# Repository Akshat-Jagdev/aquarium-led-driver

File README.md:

# Aquarium LED Driver Panel (V0)

Open-source hardware project: a scientifically engineered aquarium LED light for fish-colour enhancement, designed for low-cost manufacture in India.

**What this repo contains — the complete engineering package:**
- **Hardware**: KiCad 8 sources for a 4-board panel (2 MCPCB LED-board designs × 2 + driver board), dual-rail +24 V/+12 V, DRC-clean layouts with scripted netlist verification
- **Firmware**: ESP32-C3 Arduino sketches — 4 light profiles, 2 kHz / 12-bit PWM, per-channel dimming
- **Engineering tools** (Python): power/thermal calculator, PWM frequency analyser, LED lifetime estimator, BOM cost calculator
- **Test procedures**: TP-01 → TP-07 (bench bring-up, optical comparison, 2-hr thermal soak, spectrum, 100-hr reliability)
- **Documentation**: design-decision rationale, driver-architecture audit (AL8860 buck topology), risk register, schematic
- **Business analysis**: unit economics, volume cost projections, competitive landscape, go-to-market

> **Stage**: V0 prototype — all 4 PCBs routed and verified, panel fabricated and received (Oct 2026); bench bring-up in progress.
> **Target retail**: ₹3,000–4,000 · **Production BOM (incl. LEDs)**: ~₹2,542 @ qty 500, ~₹2,340 @ qty 1000 · **Target**: ≤₹2,000 @ qty 5000+

---

## 1. Project Structure

```
aquarium_v0/
├── README.md                      ← this file (master index)
│
├── docs/
│   ├── 00_project_brief.md        ← full business + product specification
│   ├── 01_design_decisions.md     ← all design choices and their rationale
│   ├── 02_audit_report.md         ← full audit of original AL8860 architecture
│   ├── 03_schematic_text.md       ← text-form schematic of V0
│   └── 04_risk_register.md        ← known risks and how to mitigate them
│
├── hardware/
│   ├── kicad_project/             ← KiCad 8 sources (schematic + 4-board PCB layout)
│   ├── mechanical/
│   │   ├── extrusion_dims.md      ← aluminium extrusion specifications
│   │   ├── pcb_layout_notes.md    ← critical PCB layout rules
│   │   └── assembly_drawing.md    ← mechanical assembly
│
├── firmware/
│   ├── pwm_test_sketch.ino        ← ESP32-C3 PWM control (4 profiles, 2 kHz)
│   ├── esp32_pin_map.md           ← ESP32-C3 pin assignment
│   └── build_instructions.md      ← how to compile and upload
│
├── bom/
│   ├── BOM_v0_prototype.csv       ← bill of materials, 1-unit pricing
│   ├── BOM_v0_production_500.csv  ← bill of materials, 500-unit pricing
│   ├── PARTS_LIST.md              ← complete parts list with verified links (all sources)
│   ├── india_suppliers.md         ← contact list for Indian distributors
│   ├── lcsc_links.md              ← direct LCSC links for every part
│   └── digikey_mouser_links.md    ← backup sourcing for parts not on LCSC
│
├── datasheets/
│   ├── AL8860_diodes.pdf          ← driver IC
│   ├── LUXEON_5050_HE_Plus.pdf    ← white LED
│   ├── LUXEON_2835_Red.pdf        ← 625 nm LED
│   ├── LUXEON_Rubix_448.pdf       ← blue LED
│   ├── LUXEON_SunPlus_660.pdf     ← deep-red LED
│   ├── LRS-35-24_meanwell.pdf     ← PSU
│   ├── WSL2512_vishay.pdf         ← current-sense resistors
│   ├── 7447783680_wurth.pdf       ← inductor
│   └── SS3100_diodes.pdf          ← schottky diode
│
├── test_procedures/
│   ├── TP-01_one_channel_bench.md ← validate ONE AL8860 on perfboard
│   ├── TP-02_full_pcb_bench.md    ← validate full V0 PCB
│   ├── TP-03_optical_compare.md   ← compare profiles A/B/C/D visually
│   ├── TP-04_thermal_2hr.md       ← 2-hour thermal soak test
│   ├── TP-05_spectrum_test.md     ← spectrometer measurement (when you have one)
│   ├── TP-06_fish_appearance.md   ← qualitative test with ornamental fish
│   └── TP-07_reliability_soak.md  ← extended run (target 100 hr)
│
├── business/
│   ├── competitive_landscape.md   ← TICA vs Chihiros vs others
│   ├── unit_economics.md          ← per-unit cost and margin model
│   ├── volume_projection.md       ← 1 / 100 / 500 / 1000 unit cost
│   └── go_to_market.md            ← retail / e-commerce / aquarium shops
│
└── tools/
    ├── power_thermal_calculator.py
    ├── bom_cost_calculator.py
    ├── pwm_freq_analyzer.py
    └── led_lifetime_estimator.py
```

---

## 2. Quick Start (Layman)

If you are new to this project and want to start building today:

1. **Read** `docs/00_project_brief.md` (15 min) — full picture
2. **Read** `docs/02_audit_report.md` (20 min) — what to build and WHY
3. **Read** `docs/03_schematic_text.md` (15 min) — exact wiring
4. **Open** `bom/BOM_v0_prototype.csv` (5 min) — list of parts to order
5. **Order parts** from `bom/PARTS_LIST.md` (complete parts list with verified links for every component, including LEDs) and `bom/lcsc_links.md` and `bom/india_suppliers.md`
6. **Follow** `test_procedures/TP-01_one_channel_bench.md` — build ONE channel first
7. **Run** `tools/power_thermal_calculator.py` — verify numbers any time
8. **When ONE channel works** → move to full KiCad PCB design

---

## 3. Critical Numbers (cheat sheet)

| Item | Value |
|------|-------|
| Input voltage | 24 V DC |
| Total power (all channels max) | ~22 W |
| PSU current (full load) | ~0.92 A |
| White current per string | 250 mA |
| Red current | 120 mA |
| Blue current | 303 mA (start conservative) |
| Deep red current | 120 mA |
| PWM frequency | 2 kHz (NOT 400 Hz) |
| PWM resolution | 12-bit |
| AL8860 count | 7 (4 white, 1 red, 1 blue, 1 deep red) |
| RSET (white / red / blue / DR) | 0.40 / 0.82 / 0.33 / 0.82 Ω |
| Inductor | 68 µH shielded, ≥0.95 A Isat |
| Schottky | 100 V / 3 A (SS3100) — NOT SS24 |
| Input cap | 22 µF / 50 V X7R 1210 (NOT 10 µF 0805) |
| LED TC limit | 85 °C |
| Fuse | 2 A slow-blow |
| Controller | ESP32-C3 SuperMini, direct GPIO → 1 kΩ → CTRL |
| (NO 2N7002) | — |

---

## 4. What you already own (or have ordered)

- 12× White LED: Luminus MP5050-240P (5700K)
- 4× Red LED: LUXEON 2835 Red 625 nm
- 2× Royal Blue LED: Cree XPGDRY-LS-0000-00501
- 2× Deep Red LED: LUXEON SunPlus 660 nm
- 1× Mean Well LRS-35-24
- 1× ESP32-C3 SuperMini

---

## 5. What you still need to order

See `bom/BOM_v0_prototype.csv` and `bom/lcsc_links.md`. Total estimate: **₹3,500–4,000** for the prototype (1 unit) including passive components, PCB, and mechanical parts.

---

## 6. Current status

- [x] Architecture defined
- [x] LEDs selected and ordered
- [x] PSU selected and ordered
- [x] Controller selected and ordered
- [x] Driver IC selected
- [x] Audit of driver architecture complete
- [x] Schematic text written
- [x] BOM with India sourcing prepared
- [x] BOM production-500 ready
- [x] PWM firmware written
- [x] Python calculators written (all 4 tools verified to run)
- [x] Test procedures drafted (TP-01 → TP-07)
- [x] Hardware mechanical documentation drafted (extrusion, PCB layout, assembly)
- [x] ESP32 pin map + build instructions
- [x] KiCad project scaffold documented
- [x] Business documents drafted (competitive landscape, unit economics, volume projection, go-to-market)
- [x] Risk register drafted
- [x] Design-decision rationale written
- [x] KiCad schematic capture (aquarium_v0.kicad_sch, Sep 14 netlist is truth)
- [x] 4-board PCB layout routed (gen_pcb.py + ROUTES_EXTRA.json; DRC clean on all boards, verify_netlist.py passes)
- [x] MCPCB + driver PCB Gerbers — panel fabricated and received (Oct 2026); see `hardware/assembly/`
- [ ] One-channel bench prototype (Phase B)
- [ ] Full PCB prototype (Phase C)
- [ ] Optical test against TICA (TP-03)
- [ ] Thermal verification (TP-04)
- [ ] Spectrum measurement (TP-05)
- [ ] Reliability soak (TP-07)
- [ ] Production design (V1)

---

## 7. Design decisions (resolved)

Before PCB layout, decide:
- Length: 60 cm or 90 cm? (DECIDED: 60 cm)
- Diffuser: clear, opal, or both? (DECIDED: opal)
- MCPCB: **DECIDED** — 4 small boards, 2 designs × 2 (5-LED, 140 × 20 mm; see `extrusion_dims.md` §3)
- Mounting: hanging kit, rim-mount bracket, or both? (DECIDED: rim-mount bracket)

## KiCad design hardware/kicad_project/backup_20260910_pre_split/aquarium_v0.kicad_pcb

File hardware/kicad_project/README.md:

# KiCad Project — V0 Aquarium Light

> Scaffold for the V0 schematic capture and PCB layout.
> Create the `.kicad_pro` and `.kicad_sch` in KiCad 8 and save them here.

## 1. How to create the project

1. Open **KiCad 8** (project editor).
2. **File → New Project** → name it `aquarium_v0` → save into this folder.
3. KiCad creates:
   - `aquarium_v0.kicad_pro` — project settings
   - `aquarium_v0.kicad_sch` — top-level schematic (initially empty)
4. Use **Schematic Editor → File → Add Sheet** to break the schematic into
   sections (recommended for readability):
   - `01_power.kicad_sch` — input, fuse, switch, 24 V bus, ESP32 power tree
   - `02_white_drivers.kicad_sch` — 4× AL8860 white channels
   - `03_colour_drivers.kicad_sch` — red + blue + deep-red AL8860 channels
   - `04_esp32_interface.kicad_sch` — ESP32 header + GPIO buffer network

## 2. Library plan

| Part | Source |
|------|--------|
| AL8860W6-7 (SOT23-6) | Diodes Inc KiCad library, or generic SOT-23-6 symbol with custom footprint |
| Würth 7447783680 (WE-PD series) | Würth WE-PD library, or KiCad "Inductor_SMD" + manual WE-PD footprint |
| Vishay WSL2512 | KiCad `Resistor_SMD:R_2512_6332Metric` |
| SS3100 (SMA) | KiCad `Diode_SMD:D_SMA` |
| ESP32-C3 SuperMini | Custom symbol + custom footprint (no KiCad library entry) |
| LUXEON 5050, 2835, Rubix | Custom symbols + footprints (see below) |
| 220 µF Nichicon UPW radial | KiCap `CP_Radial_D10.0mm_P5.00mm` or similar |
| Mean Well LRS-35-24 | Mechanical only — represented as off-board connector |
| IRM-02-5 | Off-board DIP module — represented as 4-pin connector |

## 3. Custom symbol / footprint list

You'll need to draw these by hand using KiCad's Symbol Editor and
Footprint Editor:

1. **ESP32-C3 SuperMini module**
   - Symbol: 1×6 header with `5V, GPIO0, GPIO1, GND, 3V3, ...` pins
   - Footprint: 2× 1×12 pin header strip, 2.54 mm pitch, board-edge
     mounting
2. **LUXEON 5050 HE Plus**
   - Symbol: LED with anode / cathode / thermal pad
   - Footprint: 5050 SMD with thermal pad
3. **LUXEON 2835 (Red and SunPlus)**
   - Symbol: LED with anode / cathode / thermal pad
   - Footprint: 2835 SMD
4. **LUXEON Rubix (L1RX-RYL1000000000)**
   - Symbol: LED with 2 anode + 2 cathode + thermal pad
   - Footprint: Rubix-style SMD with thermal pad

## 4. Net classes

Define these in **Project → Design Rules → Net Classes**:

| Net class | Clearance | Track width | Via drill | Use |
|-----------|-----------|-------------|-----------|-----|
| Default | 0.15 mm | 0.20 mm | 0.3 mm | Signals, CTRL, 3V3 |
| Power_24V | 0.30 mm | 0.50 mm | 0.5 mm | 24 V bus |
| LED_Anode | 0.30 mm | 1.00 mm | 0.5 mm | LED anode traces (250 mA) |
| LED_Cathode | 0.30 mm | 0.80 mm | 0.5 mm | LED cathode / RSET |

## 5. Layout checklist (before generating Gerbers)

- [ ] Board outline: ~580 × ≤14 mm slender strip (extrusion cavity) — see
      `../mechanical/pcb_layout_notes.md` §1
- [ ] MCPCB headers J2–J5: 6-pin each, pinout per `pcb_layout_notes.md` §3.2
      (colour series chains completed with PCB traces between headers)
- [ ] All decoupling caps within 2 mm of their IC pin (AL8860 × 7)
- [ ] Switching loop (LX, L, D1) area < 50 mm² per channel
- [ ] 100 mm² thermal copper under each AL8860, stitched with vias
- [ ] ESP32 section separated from 24 V section by ≥ 10 mm
- [ ] All MCPCB connectors labelled + and −
- [ ] Fuse clearly marked F1 with value
- [ ] Mounting holes dimensioned and clear of copper
- [ ] DRC clean, no warnings

## 6. Fabrication output

Export Gerbers + drill files into `hardware/kicad_project/gerbers/` and
zip them before uploading to JLCPCB / PCBWay. Use these settings:

- Layers: top, bottom, silkscreen top, soldermask top + bottom
- 1.6 mm board thickness
- 1 oz copper
- HASL-lead-free finish (cheapest) or ENIG (better for hand soldering)
- 4× M3 mounting holes plated (or non-plated — cheaper, fine for our use)

## 7. Open items

- Final ESP32-C3 SuperMini symbol/footprint geometry — measure from the
  physical board before drawing
- Confirm Mean Well IRM-02-5 pinout from datasheet before symbolising
- Decide whether to use 2 oz copper for the LED anode traces (cleaner
  at high current, +₹30 per board)

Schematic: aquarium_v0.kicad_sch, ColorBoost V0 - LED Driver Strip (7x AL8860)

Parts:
C1, C20, C21, C22, C23, C24, C25, C26: 100nF; C_0603_1608Metric
C2: 220uF/50V; CP_Radial_D10.0mm_P5.00mm
C3, C4: 1uF; C_0805_2012Metric
C10, C11, C12, C13, C14, C15, C16: 22uF; C_1210_3225Metric
D1, D2, D3, D4, D5, D6, D7: SS3100; D_SMA
F1: 2A slow-blow; Fuseholder_Clip-5x20mm_Littelfuse_520_Inline_P20.50x5.80mm_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
J1: DC 24V IN; TerminalBlock_MaiXu_MX126-5.0-02P_1x02_P5.00mm
J2: MCPCB1 (L1, blue); PinHeader_1x06_P2.54mm_Vertical
J3: MCPCB2 (L2, blue); PinHeader_1x06_P2.54mm_Vertical
J4: MCPCB3 (R1, deep-red); PinHeader_1x06_P2.54mm_Vertical
J5: MCPCB4 (R2, deep-red); PinHeader_1x06_P2.54mm_Vertical
J6: ESP32-C3; PinHeader_1x06_P2.54mm_Vertical
J7: SW LOOP; TerminalBlock_MaiXu_MX126-5.0-02P_1x02_P5.00mm
L1, L2, L3, L4, L5, L6, L7: 68uH; L_7.3x7.3_H3.5
MH1, MH2, MH3, MH4: M3; MountingHole_3.2mm_M3
R1, R2, R3, R4: 1k; R_0603_1608Metric
R5, R6, R7, R8: 100k; R_0603_1608Metric
R10, R11, R12, R13: 0.40R; R_2512_6332Metric
R14, R16: 0.82R; R_2512_6332Metric
R15: 0.33R; R_2512_6332Metric
U1, U2, U3, U4, U5, U6, U7: AL8860WT-7; TSOT-23-5
U8: IRM-02-5; PinHeader_1x04_P2.54mm_Vertical
U9: AMS1117-3.3; SOT-223

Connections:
+3V3: C4.2, J6.6, U9.2 (VO)
+5V: C3.2, U8.3 (+VOUT), U9.3 (VI)
/B_A: J2.5, R15.1, U6.4 (SET)
/B_J23: J2.6, J3.5
/B_K: J3.6, L6.2
/CTRL_B: R3.1, R7.2, U6.3 (CTRL)
/CTRL_DR: R4.1, R8.2, U7.3 (CTRL)
/CTRL_R: R2.1, R6.2, U5.3 (CTRL)
/CTRL_W: R1.1, R5.2, U1.3 (CTRL), U2.3 (CTRL), U3.3 (CTRL), U4.3 (CTRL)
/DR_A: J4.5, R16.1, U7.4 (SET)
/DR_J45: J4.6, J5.5
/DR_K: J5.6, L7.2
/PWM_B: J6.3, R3.2
/PWM_DR: J6.4, R4.2
/PWM_R: J6.2, R2.2
/PWM_W: J6.1, R1.2
/R_A: J2.3, R14.1, U5.4 (SET)
/R_J23: J2.4, J3.3
/R_J34: J3.4, J4.3
/R_J45: J4.4, J5.3
/R_K: J5.4, L5.2
/SW_A: F1.2, J7.1
/VIN_RAW: F1.1, J1.1
/W1_A: J2.1, R10.1, U1.4 (SET)
/W1_K: J2.2, L1.2
/W2_A: J3.1, R11.1, U2.4 (SET)
/W2_K: J3.2, L2.2
/W3_A: J4.1, R12.1, U3.4 (SET)
/W3_K: J4.2, L3.2
/W4_A: J5.1, R13.1, U4.4 (SET)
/W4_K: J5.2, L4.2
unnamed: D1.2, L1.1, U1.1 (SW)
unnamed: D2.2, L2.1, U2.1 (SW)
unnamed: D3.2, L3.1, U3.1 (SW)
unnamed: D4.2, L4.1, U4.1 (SW)
unnamed: D5.2, L5.1, U5.1 (SW)
unnamed: D6.2, L6.1, U6.1 (SW)
unnamed: D7.2, L7.1, U7.1 (SW)

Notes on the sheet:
POWER INPUT: J1 (panel jack leads) -> F1 2A slow-blow -> J7 (panel switch loop) -> +24V bus
LOGIC POWER: IRM-02-5 24V->5V, AMS1117 5V->3V3. VERIFY IRM-02-5 PINOUT VS DATASHEET.
ESP32-C3 SuperMini plugs onto J6. GPIO0-3 -> 1k -> CTRL_x; 100k pull-downs keep LEDs off during boot.
LED DRIVER CHANNELS (7x AL8860WT-7, TSOT-25). High-side sense: +24V -> RSET -> SET pin = LED string anode; string cathode -> L -> SW; D freewheels SW -> +24V. I_LED = 0.1V / RSET.
MCPCB HEADERS: J2-J5 -> LED boards. Red chain J2>J3>J4>J5, blue J2>J3, deep-red J4>J5 (series joins on this PCB).
AL8860 RESOLVED 2026-09-08: 'AL8860W6-7 SOT-23-6' DOES NOT EXIST (LCSC C460356 = AP3012 boost, wrong part). Use AL8860WT-7 TSOT-25, LCSC C125330. Pinout per DS39014: 1=SW 2=GND 3=CTRL 4=SET 5=VIN.

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
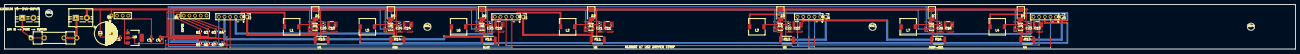
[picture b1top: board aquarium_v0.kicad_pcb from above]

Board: 2 copper layers, 580.0 x 20.0 mm, 68 parts (0 on the bottom side), 40 nets.

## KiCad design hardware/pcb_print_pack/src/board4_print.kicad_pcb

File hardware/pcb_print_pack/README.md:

# DIY PCB Print Pack — aquarium_v0 driver boards (4 boards)

Everything you need to make the 4 driver boards **at home** (toner
transfer or UV photoresist), generated 2026-09-12 from the verified,
DRC-clean split boards. The artwork is byte-equivalent to the fab
boards, only translated so each board sits at an 8 mm margin on an
A4 page (the fab files plot at the original 580 mm-frame coordinates
and run off the page).

```
pcb_print_pack/
├── board1/ … board4/          one folder per board
│   ├── print/                 6 printable PDFs (A4 landscape, 1:1)
│   ├── drill/                 Excellon .drl + hole-map PDF + report
│   └── gerber/                full 7-layer fab set (if you give up
│                              and send them to JLCPCB after all 😉)
└── src/                       the translated KiCad files used to plot
                               everything (open in KiCad to re-plot)
```

| Board | Size (mm) | Vias | Plated holes | Unplated (M3) |
|-------|-----------|------|--------------|----------------|
| 1 | 150.5 × 20 | 31 | 69 | 2 |
| 2 | 149.0 × 20 | 44 | 72 | 2 |
| 3 | 97.9 × 20 | 26 | 52 | 2 |
| 4 | 175.1 × 20 | 34 | 50 | 2 |

## 1. Printing — the one rule that matters

**Print at 100% / "Actual size". Never "fit to page" or "shrink
oversized pages".** Laser printer, highest resolution/darkest setting.

**Scale check (mandatory, every print):** print `boardN_Edge_Cuts.pdf`
and measure the board outline width with a steel ruler:
B1 **150.5 mm**, B2 **149.0 mm**, B3 **97.9 mm**, B4 **175.1 mm**
(±0.2 mm). If it doesn't match, your printer is scaling — fix that
before wasting copper.

## 2. Which PDF for which method

Two copper artwork files per side — the right one depends on how you
apply it:

| Method | Top copper (F.Cu) | Bottom copper (B.Cu) |
|--------|-------------------|----------------------|
| **Toner transfer** (paper laid face-down on the copper) | `boardN_F_Cu_MIRRORED.pdf` | `boardN_B_Cu_BOTTOM-SIDE.pdf` |
| **UV photoresist** (transparency laid on top of the copper) | `boardN_F_Cu_TOP-SIDE.pdf` | `boardN_B_Cu_MIRRORED.pdf` |

For photoresist, print on transparency with the **ink side facing the
board** (flip the film over after printing) so the ink touches the
resist — sharpness.

Other files:
- `boardN_F_Silkscreen.pdf` — component-placement reference. Your home
  board will have no real silkscreen: print this and keep it next to
  you while stuffing. It also shows the board title and pin-1 markers.
- `boardN_Edge_Cuts.pdf` — board outline, also your scale check.
- Ground pours are part of the copper artwork — don't "simplify" them
  away; they carry the GND net.

## 3. Drilling

Hole sizes (from `drill/drill_report.txt` / the map PDF
`boardN_print-drl_map.pdf`):

| Size | Use | Boards | Home-shop advice |
|------|-----|--------|------------------|
| 0.3 mm | signal vias | all | **See §4 — do NOT hand-drill 0.3 mm.** |
| 1.0 mm | header/component pins (J1–J13) | all | 1.0 mm carbide bit |
| 1.3 mm | fuse clips (F1) | 1 only | 1.3 mm bit |
| 3.2 mm | M3 mounting holes (NPTH) | all | 3.2 mm; use as top/bottom **alignment pins** |

Drill AFTER etching, BEFORE solder mask/assembly. Use the drill-map
PDF as your hole template; a small drill press beats a hand drill —
the board is only 20 mm wide, so mark hole centers with a center punch
first.

## 4. The vias — read this before etching

The 0.3 mm via drill is at the limit of home tooling, and a via pad is
only 0.8 mm across — **oversizing the hole to 0.6–0.8 mm eats the
whole annular ring**. The reliable home method is **through-wire vias**:

1. Drill the vias at 0.6–0.8 mm (don't try 0.3 mm).
2. Thread each via with a strand of tinned copper wire (unwrap a
   strand from stranded wire, or use resistor-lead clippings).
3. Solder BOTH sides, then snip flush.

31/44/26/34 vias on boards 1–4 — an evening of threading. There is no
via on this board you can skip: the CTRL ladder and colour chains
change layers through them.

## 5. Two-layer alignment

- Etch the top side first, then flip the SAME copper-clad board for
  the bottom.
- Use the two 3.2 mm M3 holes as registration: after etching top,
  push two 3.2 mm pins (or drill bits) through and align the bottom
  artwork/film to them before exposure/transfer.
- Boards are 20 mm wide and all vias are through-wired, so a small
  top/bottom offset (<0.3 mm) is tolerable — but check before etching,
  not after.

## 6. Honest warnings

- **Min track 0.25 mm / min clearance 0.25 mm** (signal netclass).
  Toner transfer can do this, but you need a clean, hot transfer —
  laser printer + glossy paper (or the blue PnP sheets), no inkjet.
  If 0.25 mm traces lift, stop and troubleshoot the transfer; don't
  accept broken signal traces. Power tracks are 0.5–1.0 mm — easy.
- **No solder mask**: the 2 kHz buck converters will survive hand
  soldering without mask, but avoid solder bridges on the 0603
  passives; flux generously and inspect under magnification.
- **The LED MCPCBs cannot be made at home** (aluminum core) — order
  those from a fab as before (see `bom/PARTS_LIST.md` §10.2).
- **U8, U9, C3, C4 on board 1 stay unpopulated** (V0 decision,
  ESP32 USB-powered) — etch them anyway, just don't stuff them.
- The joints between boards need J8–J13 pin headers + 3 jumper
  harnesses (see `hardware/mechanical/pcb_layout_notes.md` §3.4) —
  a home-made board is fine for this; the headers are ordinary 2.54 mm
  breakaway strip.
- If a board gets ruined, the `gerber/` folder per board is a complete
  fab set — you can always send just that board to JLCPCB.

## 7. Verification you can do at home

1. Multimeter continuity: +24V pad to each RSET pin-2, GND ring
   continuity across the pour, no +24V-to-GND shorts before the
   drivers are stuffed.
2. Eyeball every trace against `boardN_F_Silkscreen.pdf` /
   the drill map under a loupe.
3. Before full population: install only the power path on board 1
   (F1, C2, J1), apply 24 V, check the fuse and no heat.
4. Then follow TP-02 (full PCB bench test) in the test plan.

## 8. Where this came from

- Source of truth: `hardware/kicad_project/aquarium_v0_board{1..4}.kicad_pcb`
  (DRC 0/0, `verify_pcb.py --board N` ALL PASS ×4, byte-reproducible).
- These print files were generated from translated copies
  (`src/board{N}_print.kicad_pcb`, outline anchored at 8 mm on A4)
  by `hardware/kicad_project/make_print_copies.py`; the translation
  is machine-verified by `check_print_copies.py` — every pad, track,
  via and zone moved by exactly the same offset, DRC re-checked 0/0.
- Regenerate everything: run `make_print_copies.py`, then re-run the
  kicad-cli exports (see the commands in the project checklist).

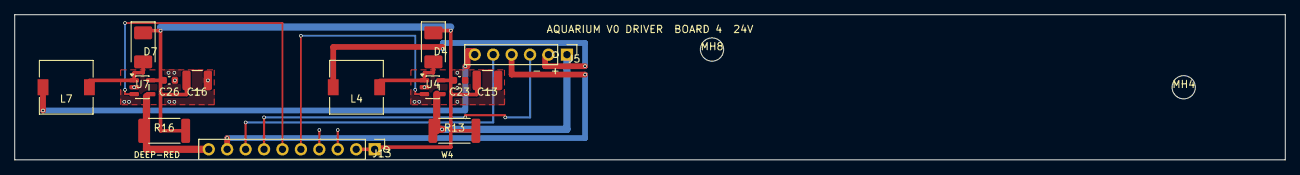
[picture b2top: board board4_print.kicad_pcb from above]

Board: 2 copper layers, 175.1 x 20.0 mm, 16 parts (0 on the bottom side), 13 nets.

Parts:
C13, C16: 22uF; C_1210_3225Metric
C23, C26: 100nF; C_0603_1608Metric
D4, D7: SS3100; D_SMA
J5: MCPCB4 (R2, deep-red); PinHeader_1x06_P2.54mm_Vertical
J13: B4-W -> J12; PinHeader_1x10_P2.54mm_Vertical
L4, L7: 68uH; L_7.3x7.3_H3.5
MH4, MH8: M3; MountingHole_3.2mm_M3
R13: 0.40R; R_2512_6332Metric
R16: 0.82R; R_2512_6332Metric
U4, U7: AL8860WT-7; TSOT-23-5

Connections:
+24V: C13.2, C16.2, C23.2, C26.2, D4.1, D7.1, J13.1, J13.2, R13.2, R16.2, U4.5, U7.5
/CTRL_DR: J13.6, U7.3
/CTRL_W: J13.5, U4.3
/DR_A: J13.10, R16.1, U7.4
/DR_J45: J5.5, J13.8
/DR_K: J5.6, L7.2
/R_J45: J5.3, J13.7
/R_K: J5.4, J13.9
/W4_A: J5.1, R13.1, U4.4
/W4_K: J5.2, L4.2
GND: C13.1, C16.1, C23.1, C26.1, J13.3, J13.4, U4.2, U7.2
unnamed: D4.2, L4.1, U4.1
unnamed: D7.2, L7.1, U7.1

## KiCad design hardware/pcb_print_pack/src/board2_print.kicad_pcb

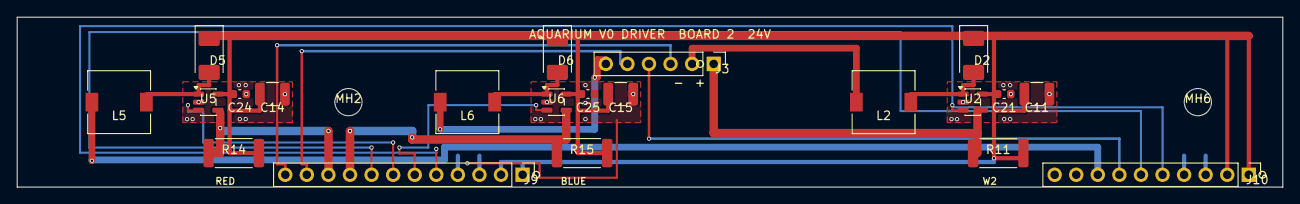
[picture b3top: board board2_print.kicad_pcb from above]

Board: 2 copper layers, 149.0 x 20.0 mm, 23 parts (0 on the bottom side), 18 nets.

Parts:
C11, C14, C15: 22uF; C_1210_3225Metric
C21, C24, C25: 100nF; C_0603_1608Metric
D2, D5, D6: SS3100; D_SMA
J3: MCPCB2 (L2, blue); PinHeader_1x06_P2.54mm_Vertical
J9: B2-W -> J8; PinHeader_1x12_P2.54mm_Vertical
J10: B2-E -> J11; PinHeader_1x10_P2.54mm_Vertical
L2, L5, L6: 68uH; L_7.3x7.3_H3.5
MH2, MH6: M3; MountingHole_3.2mm_M3
R11: 0.40R; R_2512_6332Metric
R14: 0.82R; R_2512_6332Metric
R15: 0.33R; R_2512_6332Metric
U2, U5, U6: AL8860WT-7; TSOT-23-5

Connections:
+24V: C11.2, C14.2, C15.2, C21.2, C24.2, C25.2, D2.1, D5.1, D6.1, J9.1, J9.2, J10.1, J10.2, R11.2, R14.2, R15.2, U2.5, U5.5, U6.5
/B_A: J9.9, R15.1, U6.4
/B_J23: J3.5, J9.11
/B_K: J3.6, L6.2
/CTRL_B: J9.6, U6.3
/CTRL_DR: J9.8, J10.6
/CTRL_R: J9.7, U5.3
/CTRL_W: J9.5, J10.5, U2.3
/R_A: J9.10, R14.1, U5.4
/R_J23: J3.3, J9.12
/R_J34: J3.4, J10.7
/R_K: J10.8, L5.2
/W2_A: J3.1, R11.1, U2.4
/W2_K: J3.2, L2.2
GND: C11.1, C14.1, C15.1, C21.1, C24.1, C25.1, J9.3, J9.4, J10.3, J10.4, U2.2, U5.2, U6.2
unnamed: D2.2, L2.1, U2.1
unnamed: D5.2, L5.1, U5.1
unnamed: D6.2, L6.1, U6.1

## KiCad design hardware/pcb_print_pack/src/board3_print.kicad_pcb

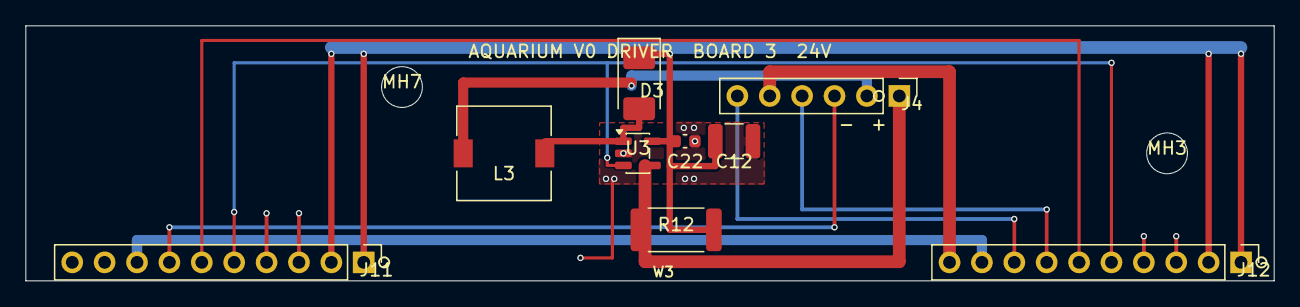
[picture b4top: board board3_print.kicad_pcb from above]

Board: 2 copper layers, 97.9 x 20.0 mm, 11 parts (0 on the bottom side), 12 nets.

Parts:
C12: 22uF; C_1210_3225Metric
C22: 100nF; C_0603_1608Metric
D3: SS3100; D_SMA
J4: MCPCB3 (R1, deep-red); PinHeader_1x06_P2.54mm_Vertical
J11: B3-W -> J10; PinHeader_1x10_P2.54mm_Vertical
J12: B3-E -> J13; PinHeader_1x10_P2.54mm_Vertical
L3: 68uH; L_7.3x7.3_H3.5
MH3, MH7: M3; MountingHole_3.2mm_M3
R12: 0.40R; R_2512_6332Metric
U3: AL8860WT-7; TSOT-23-5

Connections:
+24V: C12.2, C22.2, D3.1, J11.1, J11.2, J12.1, J12.2, R12.2, U3.5
/CTRL_DR: J11.6, J12.6
/CTRL_W: J11.5, J12.5, U3.3
/DR_A: J4.5, J12.10
/DR_J45: J4.6, J12.8
/R_J34: J4.3, J11.7
/R_J45: J4.4, J12.7
/R_K: J11.8, J12.9
/W3_A: J4.1, R12.1, U3.4
/W3_K: J4.2, L3.2
GND: C12.1, C22.1, J11.3, J11.4, J12.3, J12.4, U3.2
unnamed: D3.2, L3.1, U3.1

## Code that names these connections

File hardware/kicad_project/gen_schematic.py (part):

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# J1: DC 24V in (panel jack leads -> screw terminal)
conn("aquarium:Conn_01x02", 1500, 2500, "J1", "DC 24V IN", TB2, 2)
wire(1500, 2500, 1500, 2600)
label("VIN_RAW", 1500, 2600)
pwr("GND", 1500, 2400)
pwr("PWR_FLAG", 1500, 2400)

# F1: fuse (5x20mm clip-in, Keystone 3527-style clips)
comp2("aquarium:Fuse", 2200, 2500, "F1", "2A slow-blow", FUSECLIP)
wire(2200, 2500, 2200, 2600)
label("VIN_RAW", 2200, 2600)
wire(2200, 2400, 2200, 2300)
label("SW_A", 2200, 2300)

# J7: panel switch loop (leads -> screw terminal)
conn("aquarium:Conn_01x02", 2900, 2500, "J7", "SW LOOP", TB2, 2)
wire(2900, 2500, 2900, 2600)
label("SW_A", 2900, 2600)
pwr("+24V", 2900, 2400)
pwr("PWR_FLAG", 2900, 2400)

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# J6: ESP32-C3 SuperMini header
conn("aquarium:Conn_01x06", 1500, 7500, "J6", "ESP32-C3", PH6, 6)
wire(1500, 7500, 1400, 7500)
label("PWM_W", 1400, 7500, 180)
wire(1500, 7400, 1400, 7400)
label("PWM_R", 1400, 7400, 180)
wire(1500, 7300, 1400, 7300)
label("PWM_B", 1400, 7300, 180)
wire(1500, 7200, 1400, 7200)
label("PWM_DR", 1400, 7200, 180)
pwr("GND", 1500, 7100)
pwr("+3V3", 1500, 7000)

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     "(B1 logic+U1+J2 | B2 U5+U6+U2+J3 | B3 U3+J4 | B4 U7+U4+J5). Each seam = "
     "2 pin headers joined off-board by a jumper harness. Pin maps are identical "
     "at both ends of each seam; seam 1 uses 1x12, seams 2-3 use 1x10 "
     "(CTRL_B/CTRL_R terminate on B2; NC pins = no wire in the harness).", 1000, 9500)
# Header sizes from the KiCad courtyard geometry (a horizontal 1x13 needs a
# 34 mm clear band; only B1 has one). /R_K (U5 on B2 -> J5 on B4) passes
# THROUGH board 3: J10-8 <-> J11-8 and J12-9 <-> J13-9.
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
